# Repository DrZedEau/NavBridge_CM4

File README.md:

# NavBridge CM4

A Raspberry Pi Compute Module 4 carrier board for BMW E-Series vehicles equipped with the OEM navigation system (E46, E39, E85, and similar platforms).

The NavBridge CM4 installs inline between the factory wiring harness and the BMW MK3/MK4 navigation module, allowing a Raspberry Pi Compute Module to integrate with the original infotainment system while preserving the OEM look and functionalities.

Its primary purpose is to provide modern features such as Android Auto and Apple CarPlay through the Raspberry Pi while continuing to use the factory display, controls, and audio system.

This revision is designed for the **Raspberry Pi CM4** and should also work with the **CM5**, which uses the same connectors (see [Using a CM5](#using-a-cm5)).

---

## Overview

The board interfaces directly with the factory navigation module and provides:

- Video output from the Raspberry Pi to the OEM BMW display (analog RGB with sync on green)
- Switching of the display between the factory navigation picture and the Raspberry Pi
- Stereo audio output for integration with the factory AUX input or CDC interface
- Microphone input
- Integration with the BMW I-Bus for power management and button control
- Two M.2 Key E expansion slots
- A CSI camera connector
- An Apple MFi authentication coprocessor

The hardware is designed to run [NavBridge App](https://github.com/DrZedEau/NavBridge_App), a standalone Android Auto head unit for the Raspberry Pi, or the [LIVI](https://github.com/f-io/LIVI) project.

---

## Features

### Hardware

- 100 × 100 mm, 4-layer PCB
- Raspberry Pi CM4 / CM5 connectors (2 × 100-pin Hirose DF40C)
- Automotive-grade 5 V / 3.5 A buck converter (**LMR14030-Q1**), switched on and off by the MCU
- Fused battery input with a **SMCJ24A** TVS diode
- USB-C port for Raspberry Pi flashing (rpiboot) and bench power, with automatic selection between USB-C and the car supply (**TPS2117**)
- 4-port USB 2.0 hub (**USB2514B**) for the MCU, the audio codec and both M.2 slots
- 24-bit video DAC (**ADV7125**) fed by the Raspberry Pi DPI output
- Analog RGB switch (**TMUX1574**) to select the factory navigation picture or the Raspberry Pi picture
- Integrated **PCM2912A** USB audio codec
  - Stereo line output
  - Mono microphone input with bias
- Two M.2 Key E slots, powered by a dedicated 3.3 V / 2 A buck converter (**AP63203**)
  - CN6: PCIe x1 + USB 2.0
  - CN7: USB 2.0 only
- 22-pin CSI camera connector (CAM1, 2 lanes) on the bottom side
- Apple **MFi343S00177** authentication coprocessor on I²C
- Auxiliary 5 V output connector
- SWD connector for the STM32

The board has no SD card slot, so it needs a Compute Module with eMMC (not a Lite module).

### Vehicle Integration

- Two **ATA663231** LIN transceivers: one on the car I-Bus, one on the navigation module's I-Bus, with the MCU in between
- **STM32C071** microcontroller for:
  - Raspberry Pi power management
  - OEM button translation
  - Composite sync (CSYNC) generation for the OEM display
  - Video source selection
- The MCU is powered from the car battery through the car-side LIN transceiver's built-in 3.3 V regulator, so it keeps watching the I-Bus while the Raspberry Pi is off
- No modifications to the factory wiring or infotainment system are required

---

## Board Overview

### Connectors

| Ref | Connector | Use |
|---|---|---|
| CN1, CN2 | Hirose DF40C-100DS | Raspberry Pi CM4 / CM5 |
| CN3 | Molex Micro-Fit 3.0, 12 pins (43045-1200) | To the navigation module |
| CN4 | 2 × 9 pin header, 2.54 mm, right angle | Car harness (X1313 connector) |
| CN5 | 2 × 5 pin header, 1.27 mm | STM32 SWD |
| CN6 | M.2 Key E | PCIe x1 + USB 2.0 module |
| CN7 | M.2 Key E | USB 2.0 module |
| CN8 | JST GH, 2 pins | Auxiliary +5 V output |
| U1 | JST GH, 3 pins | Stereo line output |
| U2 | JST GH, 2 pins | Microphone input |
| U18 | 22-pin FPC, 0.5 mm (bottom side) | CSI camera (CAM1) |
| J1 | USB-C | Raspberry Pi flashing and bench power |

#### CN4 – Car harness

| Pin | Signal | Pin | Signal |
|---|---|---|---|
| 1 | +BATT | 2 | GND |
| 3 | – | 4 | – |
| 5 | I-Bus | 6 | GND |
| 7 | – | 8 | – |
| 9 | Green out | 10 | GND |
| 11 | Blue out | 12 | GND |
| 13 | Red out | 14 | GND |
| 15 | – | 16 | – |
| 17 | Nav audio + | 18 | Nav audio − |

#### CN3 – Navigation module

| Pin | Signal | Pin | Signal |
|---|---|---|---|
| 1 | GND | 7 | +BATT |
| 2 | GND | 8 | I-Bus (navigation side) |
| 3 | GND | 9 | Red in |
| 4 | GND | 10 | Green in |
| 5 | GND | 11 | Blue in |
| 6 | Nav audio − | 12 | Nav audio + |

+BATT and the navigation audio pass straight through between CN3 and CN4. The I-Bus does not: the car I-Bus (CN4 pin 5) and the navigation module's I-Bus (CN3 pin 8) each have their own ATA663231 transceiver, and the STM32 passes messages between them. The red, green and blue signals from the navigation module go through the RGB switch before reaching the display.

#### Audio connectors

| Connector | Pin 1 | Pin 2 | Pin 3 |
|---|---|---|---|
| U2 (microphone) | MIC in | GND | |
| U1 (line out) | Left | GND | Right |
| CN8 (aux power) | +5 V | GND | |

### Buttons and LEDs

| Silkscreen | Part | Function |
|---|---|---|
| nRPIBOOT | SW1 (slide switch) | Pulls the CM `nRPIBOOT` low and routes the CM USB port to the USB-C connector, for flashing with rpiboot |
| RESET | SW2 | STM32 reset |
| BOOT | SW3 | STM32 BOOT0, to start the USB DFU bootloader |
| PWR | D2 (red) | CM power LED |
| ACT | D1 (green) | CM activity LED |
| STAT | D6 (yellow) | STM32 status LED |

### Power

```text
+BATT ─┬─ fuse ─ TVS ─ LMR14030 5 V buck (enabled by MCU) ─┐
       │                                                   ├─ TPS2117 ─ +5 V ─ CM and peripherals
       │                                 USB-C 5 V ────────┘
       │
       └─ diode ─ ATA663231 (car I-Bus) ─ 3.3 V ─┐
                                                 ├─ TPS2117 ─ 3.3 V ─ STM32, RGB switch
                          CM 3.3 V output ───────┘

+5 V ─ TLV75533 LDO ─ 3.3 V ─ USB hub, USB switch, video DAC (through a ferrite bead)
+5 V ─ AP63203 buck ─ 3.3 V ─ M.2 slots, camera
+5 V ─ TPS2051B switch ─ PCM2912A audio codec
```

The battery fuse holder (FH1) takes a Littelfuse 0451003.MRL (3 A) fuse, fitted by hand after assembly.

The TPS2117 selects between the car supply and USB-C automatically, so the board can be powered on the bench from USB-C alone.

### Video

The Raspberry Pi drives the **ADV7125** video DAC through its 24-bit DPI interface. The STM32 combines the DPI `HSYNC` and `VSYNC` into a composite sync (`CSYNC`) with a hardware timer and feeds it to the DAC, which adds it to the green channel (RGsB) as the BMW display expects.

The **TMUX1574** switch, controlled by the STM32, selects which picture reaches the display: the Raspberry Pi or the factory navigation module.

### USB

The CM USB 2.0 port goes through a **TS3USB221** switch controlled by the nRPIBOOT switch:

- **nRPIBOOT off** (normal use): CM → **USB2514B** hub → STM32, PCM2912A codec, M.2 slot CN6, M.2 slot CN7
- **nRPIBOOT on**: CM → USB-C connector, to flash the eMMC with rpiboot

---

## Using a CM5

The CM5 uses the same connectors as the CM4 and keeps the CM4 pinout for the interfaces this board uses (DPI, USB 2.0, PCIe, CSI camera, I²C, `nRPIBOOT`, LEDs), so it should work on this board. It has not been tested yet. A few points to keep in mind:

- The CM5's USB 3.0 ports are not used.
- CSYNC is generated by the STM32, so the board does not rely on the CM5's RP1 PIO as the [CM5 NavBridge](https://github.com/DrZedEau/CM5_NavBridge) did.
- The 5 V rail comes from a 3.5 A buck converter. A CM5 under heavy load, together with power-hungry M.2 or USB devices, can get close to that limit.
- The CM5 runs hotter than the CM4; leave room for a heatsink in the case.

---

## Repository Structure

```text
hardware/      KiCad project (revision 0.2) and the revision 0.1 archive
firmware/      STM32C071 MCU firmware
scripts/       Raspberry Pi setup script
3D/            STL files for printed parts (case and connector)
images/        Pictures and renders
```

The KiCad project in [hardware/](hardware/) was made with KiCad 10 and includes its symbol, footprint and 3D model libraries.

---

## Project Status

Revision 0.2 is the current revision of the CM4 board. Revision 0.1 is kept as an archive in [hardware/](hardware/).

- [x] Schematic and PCB layout
- [ ] Prototype testing
- [ ] STM32 firmware (the CSYNC generator has been validated on a NUCLEO-C071RB)
- [ ] Raspberry Pi setup script
- [ ] 3D printed case and connector

---

## Roadmap

- Test the first prototypes in the car
- Test with a CM5
- Expand compatibility testing across additional BMW platforms

---

## Contributing

Contributions are welcome.

Bug reports, hardware improvements, firmware enhancements, and documentation updates are all appreciated. Please open an issue or submit a pull request if you would like to contribute.

---

## License

Copyright 2026 DrZedEau

The hardware design — the KiCad project in `hardware/`, the 3D printed parts in `3D/` and the images in `images/` — is licensed under the **CERN Open Hardware Licence Version 2 – Strongly Reciprocal** (CERN-OHL-S-2.0), see [LICENSE](LICENSE). You may redistribute and modify it and make products from it under the terms of that licence. It is distributed without any express or implied warranty, including of merchantability, satisfactory quality and fitness for a particular purpose.

Source location: https://github.com/DrZedEau/NavBridge_CM4

As required by section 4 of the CERN-OHL-S, products made from this design must, where practicable, keep this source location visible.

The firmware in `firmware/` and the Raspberry Pi setup script in `scripts/` are licensed under the **GNU General Public License v2.0** (GPL-2.0), see [firmware/LICENSE](firmware/LICENSE) and [scripts/LICENSE](scripts/LICENSE). Third-party files keep their own licences.

---

## References

- CM5 NavBridge (previous board) https://github.com/DrZedEau/CM5_NavBridge
- NavBridge App https://github.com/DrZedEau/NavBridge_App
- LIVI project https://github.com/f-io/LIVI
- Raspberry Pi CM4 datasheet https://datasheets.raspberrypi.com/cm4/cm4-datasheet.pdf
- BMW Wiring Diagram System (WDS) https://bmwteka.com/wds/en/e85/e82460cf
- BMW On-Board Monitor documentation https://bmwteka.com/wds/en/e85/1b7f9876
- Community resources https://www.e46fanatics.com/threads/bmw-on-board-monitor-without-navigation-unit.1303552

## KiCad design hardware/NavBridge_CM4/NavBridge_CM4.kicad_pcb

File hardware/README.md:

# Hardware

KiCad project for the NavBridge CM4 board.

| Path | Content |
|---|---|
| `NavBridge_CM4/` | Revision 0.2 (current): schematics, PCB layout, project-local symbol, footprint and 3D model libraries |
| `NavBridge_CM4/production/` | JLCPCB fabrication files for revision 0.2 (Gerber archive, BOM, pick-and-place), made with the Fabrication Toolkit plugin |
| `NavBridge_CM4_0.1.zip` | Revision 0.1 (archive) |

The project was made with **KiCad 10**. Open `NavBridge_CM4/NavBridge_CM4.kicad_pro`.

The project-local libraries only include the 3D models used on the board. The other models come from the standard KiCad library (`KICAD10_3DMODEL_DIR`, and `KICAD9_3DMODEL_DIR` for a few footprints).

## Board

- 100 × 100 mm, 4 copper layers, 1.6 mm
- 4 × M2.5 mounting holes at the corners (3 mm from each edge)
- 4 × M2.5 mounting holes for the Compute Module
- GND stitching vias around the board edge and across the ground pours
- The battery fuse holder (FH1) takes a Littelfuse 0451003.MRL (3 A) fuse, fitted by hand after assembly

## Schematic sheets

| Sheet | Content |
|---|---|
| NavBridge_CM4 | CM4 / CM5 connectors, car connectors, audio connectors, LEDs, mounting holes |
| Power | Battery input, LMR14030 5 V buck, USB-C connector, TPS2117 power mux, TLV75533 3.3 V LDO |
| MCU_Lin | STM32C071 MCU, two ATA663231 LIN transceivers (car I-Bus and navigation I-Bus), TPS2117 MCU power mux, SWD connector |
| Analog_RGB | ADV7125 video DAC, TMUX1574 RGB switch, 75 Ω termination |
| USB | USB2514B hub, TS3USB221 USB switch |
| Audio | PCM2912A USB audio codec and its power switch |
| M.2 | Two M.2 Key E slots, AP63203 3.3 V buck, auxiliary 5 V connector |
| Misc | Apple MFi authentication coprocessor, CSI camera connector |
| SD_Card | Empty: the SD card slot was removed in revision 0.2 |

## License

CERN-OHL-S-2.0, see [LICENSE](../LICENSE).

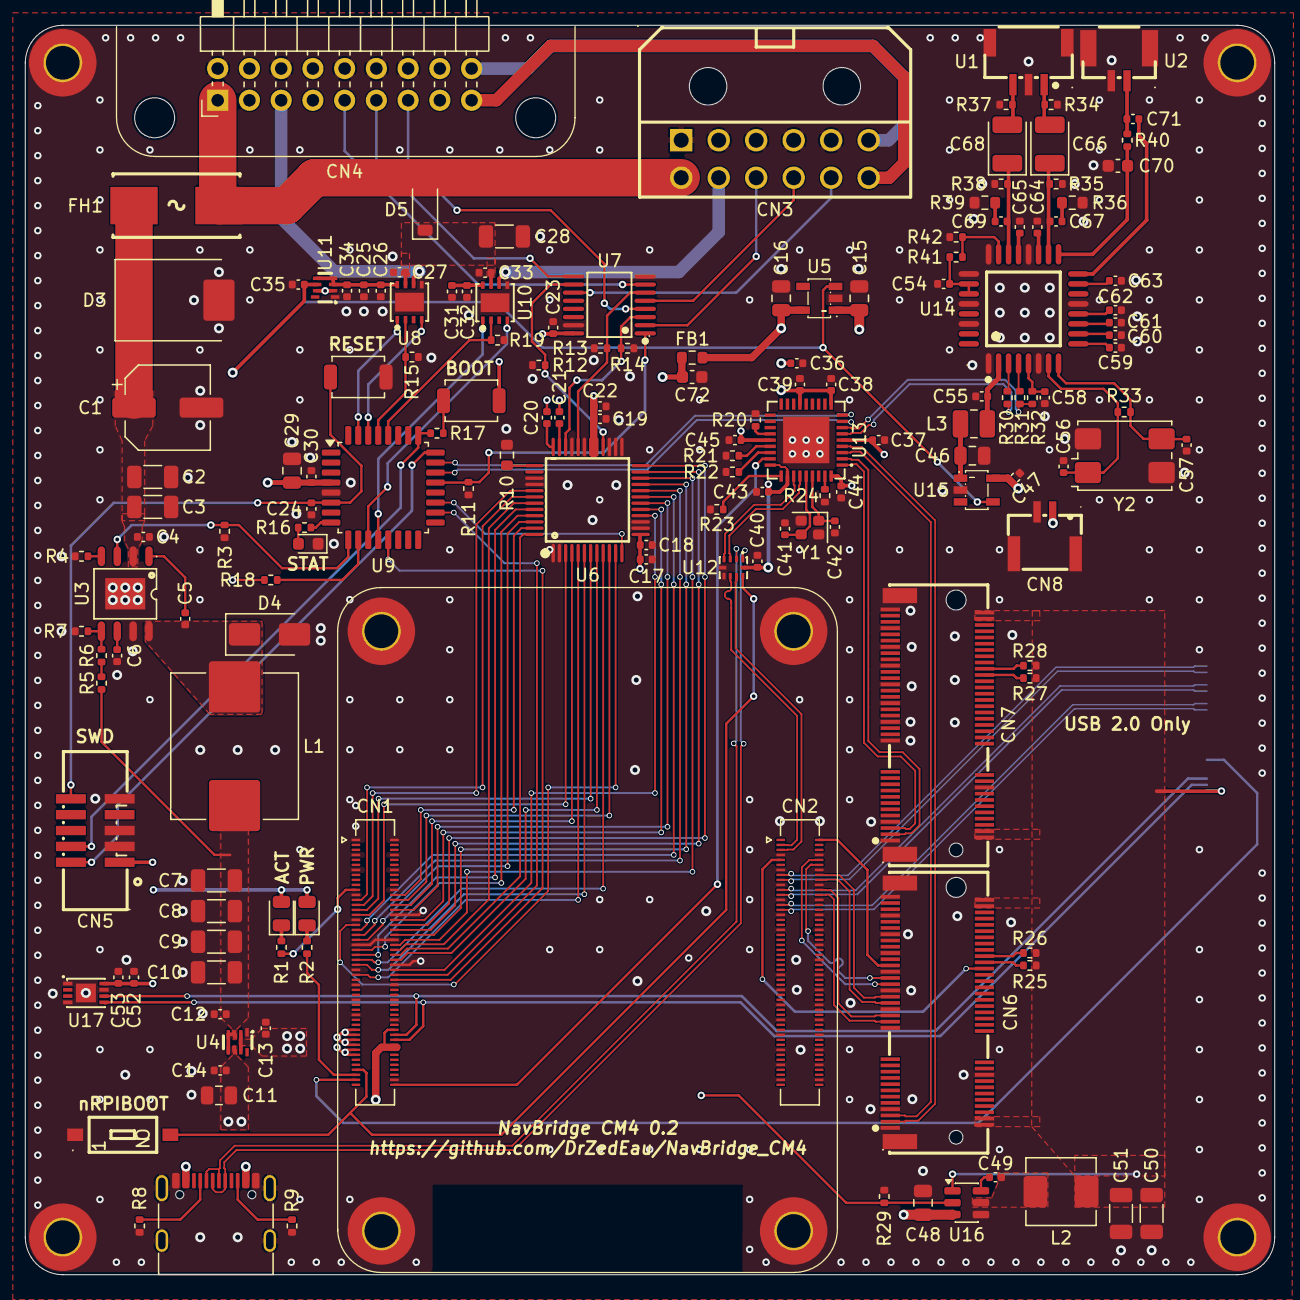
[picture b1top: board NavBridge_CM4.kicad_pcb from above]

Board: 4 copper layers, 100.0 x 100.0 mm, 165 parts (1 on the bottom side), 157 nets.

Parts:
C1: 100µ; CP_Elec_6.3x5.8
C2, C3: 4.7µ; C_1206_3216Metric
C4, C5, C6, C12, C13, C14, C18, C19, C20, C21, C23, C24, C26, C27, C30, C32, C33, C34, C35, C37, C38, C39, C40, C43, C44, C45, C47, C49, C53, C62: 100n; C_0402_1005Metric
C7, C8, C9, C10: 47µ; C_1206_3216Metric
C11, C15, C29: 4.7µ; C_0805_2012Metric
C16, C46, C48: 10µ; C_0805_2012Metric
C17, C22: 10n; C_0402_1005Metric
C25, C31, C61: 4.7µ; C_0402_1005Metric
C28: 10µ; C_1206_3216Metric
C36, C52, C54, C55, C58, C63, C64, C65, C71: 1µ; C_0402_1005Metric
C41, C42: 10p; C_0402_1005Metric
C50, C51: 22µ; C_1206_3216Metric
C56, C57: 22p; C_0402_1005Metric
C59, C60: 100p; C_0402_1005Metric
C66, C68: 100µ; CP_EIA-3528-21_Kemet-B
C67, C69: 22n; C_0402_1005Metric
C70, C72: 10µ; C_0603_1608Metric
CN1, CN2: DF40C-100DS-0.4V; Hirose_DF40C-100DS-0.4V_2x50_P0.4mm
CN3: Molex 430451200; C277636_CONN-TH_12P-P3_00-S3_00_L12_2-W21_7-EH10_7
CN4: X1313 Car connector; PinHeader_2x09_P2.54mm_Horizontal
CN5: 20021521-00010C1LF; C598547_IDC-SMD_10P-P1_27_X1270WVS-2X05B-6TV01
CN6, CN7: 2199230-4_C2977809; C2977809_PCIE-SMD_2199230-4
CN8: BM02B-GHS-TBT (LF)(SN); C161690_CONN-SMD_2P-P1_25_BM02B-GHS-TBT-LF-SN
D1: LED_G; LED_0805_2012Metric
D2: LED_R; LED_0805_2012Metric
D3: SMCJ24A; D_SMC
D4: SS54; D_SMA
D5: 1N4148W; D_SOD-123
D6: LED_Y; LED_0603_1608Metric
FB1: FerriteBead; R_0603_1608Metric
FH1: 01550900M; C108518_FUSE-SMD_L9_8-W5_0_01550900M
H1, H2, H3, H4, H5, H6, H7, H8: MountingHole_Pad; MountingHole_2.7mm_M2.5_Pad_TopBottom
J1: USB_C_Receptacle_USB2.0_16P; USB_C_Receptacle_G-Switch_GT-USB-7010ASV
L1: 6.8uH; L_Sunlord_MWSA1003S
L2: 6.8uH; L_Sunlord_MWSA0518S
L3: 1µH; L_1008_2520Metric
R1, R2, R16, R17, R18, R40: 1k; R_0402_1005Metric
R3, R11, R15, R19, R25, R26, R27, R28, R29: 10k; R_0402_1005Metric
R4: 49.9k; R_0402_1005Metric
R5, R20, R21, R22, R23, R42: 100k; R_0402_1005Metric
R6, R8, R9: 5.1k; R_0402_1005Metric
R7: 18k; R_0402_1005Metric
R10: 560; R_0603_1608Metric
R12, R13, R14: 75; R_0402_1005Metric
R24: 12K; R_0402_1005Metric
R30, R31: 22; R_0402_1005Metric
R32: 1.5k; R_0402_1005Metric
R33: 1M; R_0402_1005Metric
R34, R35, R37, R38: 3.3k; R_0402_1005Metric
R36, R39: 15; R_0603_1608Metric
R41: 0; R_0402_1005Metric
SW1: CHS-01B1; C3312309_SW-SMD_NIDEC_CHS-01B1
SW2, SW3: SW_Push; SW_SPST_TS-1088-xR020
U1: SM03B-GHS; C514175_CONN-TH_SM03B-GHS-TB-LF-SN
U2: SM02B-GHS; C189893_CONN-SMD_SM02B-GHS-TB-LF-SN
U3: LMR14030SQDDARQ1; C485817_SO-8_L4_9-W3_9-P1_27-LS6_0-BL-EP
U4, U11: TPS2117DRLR; C22399676_SOT-583-8_L2_1-W1_2-P0_50-LS1_6-BL
U5: TLV75533PDBVR; C404027_SOT-23-5_L3_0-W1_7-P0_95-LS2_8-BR
U6: ADV7125KSTZ140; LQFP-48_L7.0-W7.0-P0.50-LS9.0-BL
U7: TMUX1574PWR; C2673443_TSSOP-16_L5_0-W4_4-P0_65-LS6_4-BL
U8, U10: ATA663231-GBQW; C5225740_DFN-8_L3_0-W3_0-P0_65-BL-EP-1
U9: STM32C071KBTx; LQFP-32_7x7mm_P0.8mm
U12: TS3USB221ARSER; C128396_UQFN-10_L2_0-W1_5-P0_50-BL
U13: USB2514BI-AEZG-TR; C58940_TQFN-36_L6_0-W6_0-P0_50-BL-EP3_7
U14: PCM2912APJTR; C475497_TQFP-32_L7_0-W7_0-P0_80-LS9_0-TL
U15: TPS2051BDBVR; C24593_SOT-23-5_L3_0-W1_7-P0_95-LS2_8-BR
U16: AP63203WU; TSOT-23-6
U17: MFI343S00177-L; C33770534_DFN-8_L3_0-W2_0-P0_50-BL-EP1_6
U18: 0524352271; C5468341_FPC-SMD_22P-P0_50_0524352271
Y1: Crystal_GND24; Crystal_SMD_2016-4Pin_2.0x1.6mm
Y2: 6MHz; Crystal_SMD_FOX_FQ7050-4Pin_7.0x5.0mm

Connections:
+3V3: C35.1, C52.1, C53.1, CN1.78, CN1.84, CN1.86, CN5.1, D1.2 (A), D2.2 (A), R18.1, R29.1, U5.3 (EN), U11.6 (VIN2), U15.4 (EN), U16.2 (EN), U17.8 (VCC)
+3V3_LDO: C16.1, C36.2, C37.2, C38.2, C39.2, C40.1, C43.1, C44.1, C45.1, FB1.1, U5.5 (OUT), U12.10 (VCC), U13.5 (VDDA33), U13.10 (VDDA33), U13.15 (VDD33), U13.23 (VDD33), U13.27 (VBUS_DET), U13.29 (VDDA33), U13.36 (VDDA33)
+3V3_LIN_REG: C25.1, C26.2, C34.2, U8.8 (VCC), U11.3 (VIN1), U11.4 (PR1), U11.5 (MODE)
+3V3_M2: C50.1, C51.1, CN6.2, CN6.4, CN6.72, CN6.74, CN7.2, CN7.4, CN7.72, CN7.74, L2.2, R25.1, R26.2, R27.1, R28.2, U16.1 (FB), U18.22
+3V3_MUX: C23.2, C29.1, C30.1, SW3.2, U7.16 (VDD), U9.4 (VDD), U11.2 (VOUT), U11.7 (VOUT)
+3V3_SENSE: R18.2, U9.10 (PA3)
+5V: C13.2, C15.2, C47.1, C48.2, CN1.77, CN1.79, CN1.81, CN1.83, CN1.85, CN1.87, CN8.1, U4.2 (VOUT), U4.7 (VOUT), U5.1 (IN), U15.5 (IN), U16.3 (IN)
+5V_BUCK: C7.1, C8.1, C9.1, C10.1, C12.1, L1.2, R5.1, U4.3 (VIN1), U4.4 (PR1), U4.5 (MODE)
+5V_USBC: C11.1, C14.1, J1.A4 (VBUS), J1.A9 (VBUS), J1.B4 (VBUS), J1.B9 (VBUS), U4.6 (VIN2)
+BATT: CN3.7, CN4.1, D5.2 (A), FH1.1
+VBUS_PCM: C46.2, L3.1, U15.1 (OUT)
/Analog_RGB/COMP: C21.2, U6.35 (COMP)
/Analog_RGB/RSET: R10.1, U6.37 (RSET)
/Analog_RGB/VREF: C20.2, U6.36 (VREF)
/Audio/PCM_MBIAS: C70.1, R40.1, U14.17 (MBIAS)
/Audio/PCM_USB_N: R30.2, U14.3 (D-)
/Audio/PCM_USB_P: R31.2, U14.4 (D+)
/Audio/PCM_VBUS: C55.1, L3.2, U14.2 (VBUS)
/Audio/PCM_VCCL: C64.1, U14.19 (VCCL)
/Audio/PCM_VCCR: C65.1, U14.21 (VCCR)
/Audio/PCM_VDD: C58.1, R32.2, U14.5 (VDD)
/Audio/PCM_VIN: C71.2, U14.16 (VIN)
/Audio/PCM_VOUTL: C66.1, C67.1, R35.2, U14.18 (VOUTL)
/Audio/PCM_VOUTR: C68.1, C69.1, R38.2, U14.22 (VOUTR)
/Audio/PCM_XTI: C57.1, R33.2, U14.8 (XTI), Y2.3
/Audio/PCM_XTO: C56.1, R33.1, U14.7 (XTO), Y2.1
/LED1: D1.1 (K), R1.1
/LED2: D2.1 (K), R2.1
/LED_nACT: CN1.21, R1.2
/LED_nPWR: CN1.95, R2.2
/M.2/BST_3V3: C49.1, U16.6 (BST)
/M.2/SW_3V3: C49.2, L2.1, U16.5 (SW)
/Power/+BATT_FUSED: C1.1, C2.1, C3.1, C4.1, D3.1 (K), FH1.2, U3.2 (VIN)
/Power/BOOT: C5.1, U3.1 (BOOT)
/Power/FB: R6.2, R7.1, U3.5 (FB)
/Power/FREQ: R4.1, U3.4 (RT/SYNC)
/Power/SS: C6.1, U3.6 (SS)
/Power/SW: C5.2, D4.1 (K), L1.1, U3.8 (SW)
AUDIO_L: C66.2, R34.2, U1.1
AUDIO_R: C68.2, R37.1, U1.3
B0: CN1.54, U6.16 (B0)
B1: CN1.34, U6.17 (B1)
B2: CN1.30, U6.18 (B2)
B3: CN1.37, U6.19 (B3)
B4: CN1.39, U6.20 (B4)
B5: CN1.40, U6.21 (B5)
B6: CN1.44, U6.22 (B6)
B7: CN1.38, U6.23 (B7)
B_NAV: CN3.11, U7.11 (S3A)
B_OUT: CN4.11, U7.9 (D3)
B_RPI: R12.2, U6.28 (IOB), U7.10 (S3B)
CAM1_C_N: CN2.27, U18.8
CAM1_C_P: CN2.29, U18.9
CAM1_D0_N: CN2.15, U18.2
CAM1_D0_P: CN2.17, U18.3
CAM1_D1_N: CN2.21, U18.5
CAM1_D1_P: CN2.23, U18.6
CSYNC: U6.12 (~SYNC), U9.19 (PA9)
Camera_GPIO: CN1.97, U18.17
DEN: CN1.35, U6.11 (~BLANK)
G0: CN1.31, U6.3 (G0)
G1: CN1.28, U6.4 (G1)
G2: CN1.55, U6.5 (G2)
G3: CN1.51, U6.6 (G3)
G4: CN1.29, U6.7 (G4)
G5: CN1.50, U6.8 (G5)
G6: CN1.49, U6.9 (G6)
G7: CN1.26, U6.10 (G7)
GND: C1.2, C2.2, C3.2, C4.2, C6.2, C7.2, C8.2, C9.2, C10.2, C11.2, C12.2, C13.1, C14.2, C15.1, C16.2, C17.1, C18.1, C19.1, C22.1, C23.1, C24.1, C25.2, C26.1, C27.1, C28.2, C29.2, C30.2, C31.2, C32.2, C33.1, C34.1, C35.2, C36.1, C37.1, C38.1, C39.1, C40.2, C41.2, C42.2, C43.2, C44.2, C45.2, C46.1, C47.2, C48.1, C50.2, C51.2, C52.2, C53.2, C54.2, C55.2, C56.2, C57.2, C58.2, C59.2, C60.2, C61.2, C62.2, C63.2, C64.2, C65.2, C70.2, C72.1, CN1.1, CN1.2, CN1.7, CN1.8, CN1.13, CN1.14, CN1.22, CN1.23, CN1.32, CN1.33, CN1.42, CN1.43, CN1.52, CN1.53, CN1.59, CN1.60, CN1.65, CN1.66, CN1.71, CN1.74, CN1.98, CN2.7, CN2.8, CN2.13, CN2.14, CN2.19, CN2.20, CN2.25, CN2.26, CN2.31, CN2.32, CN2.37, CN2.38, CN2.44, CN2.50, CN2.55, CN2.56, CN2.61, CN2.62, CN2.67, CN2.68, CN2.73, CN2.74, CN2.79, CN2.80, CN2.85, CN2.86, CN2.91, CN2.92, CN2.97, CN2.98, CN3.1, CN3.2, CN3.3, CN3.4, CN3.5, CN4.2, CN4.6, CN4.10, CN4.12, CN4.14, CN5.3, CN5.5, CN5.9, CN6.1, CN6.7, CN6.18, CN6.33, CN6.39, CN6.45, CN6.51, CN6.57, CN6.63, CN6.69, CN6.75, CN6.76, CN6.77, CN7.1, CN7.7, CN7.18, CN7.33, CN7.39, CN7.45, CN7.51, CN7.57, CN7.63, CN7.69, CN7.75, CN7.76, CN7.77, CN8.2, CN8.3, CN8.4, D3.2 (A), D4.2 (A), D6.1 (K), H1.1 (1_1), H2.1 (1_1), H3.1 (1_1), H4.1 (1_1), H5.1 (1_1), H6.1 (1_1), H7.1 (1_1), H8.1 (1_1), J1.A1 (GND), J1.A12 (GND), J1.B1 (GND), J1.B12 (GND), J1.SH (SHIELD), R3.2, R4.2, R7.2, R8.2, R9.2, R10.2, R11.2, R12.1, R13.1, R14.1, R15.2, R19.2, R20.1, R21.2, R22.1, R23.2, R24.2, R29.2, R34.1, R35.1, R36.2, R37.2, R38.1, R39.2, R42.2, SW1.1 (PIN1), SW2.1, U1.2, U1.4, U1.5, U2.2, U2.3, U2.4, U3.7 (GND), U3.9 (EP), U4.1 (GND), U5.2 (GND), U6.1 (GND), U6.2 (GND), U6.14 (GND), U6.15 (GND), U6.25 (GND), U6.26 (GND), U6.27 (~IOB), U6.31 (~IOG), U6.33 (~IOR), U6.39 (GND), U6.40 (GND), U7.8 (GND), U7.15 (EN#), U8.5 (GND), U8.9 (EP), U9.5 (VSS), U10.5 (GND), U10.9 (EP), U11.1 (GND), U12.5 (GND), U12.6 (OE#), U13.37 (EP), U14.1 (BGND), U14.6 (DGND), U14.13 (AGND), U14.20 (HGND), U14.24 (POWER), U14.25 (PGND), U14.28 (TEST0), U14.30 (MMUTE), U15.2 (GND), U16.4 (GND), U17.1 (GND), U17.4 (GND), U17.7 (GND), U17.9 (EP), U18.1, U18.4, U18.7, U18.10, U18.13, U18.16, U18.19, U18.23, U18.24, Y1.2 (G), Y1.4 (G), Y2.2 (G), Y2.4 (G)
G_NAV: CN3.10, U7.5 (S2A)
G_OUT: CN4.9, U7.7 (D2)
G_RPI: R13.2, U6.32 (IOG), U7.6 (S2B)
HSYNC: CN1.56, U9.18 (PA8)
IBUS_CAR: CN4.5, U8.6 (LIN)
IBUS_NAV: CN3.8, U10.6 (LIN)
MCU_BUCK_EN: R3.1, U3.3 (EN), U9.9 (PA2)
MCU_LIN1_EN: R15.1, U8.2 (EN), U9.29 (PB5)
MCU_LIN1_RX: U8.1 (RXD), U9.31 (PB7)
MCU_LIN1_TX: U8.4 (TXD), U9.30 (PB6)
MCU_LIN2_EN: R19.1, U9.28 (PB4), U10.2 (EN)
MCU_LIN2_RX: U9.12 (PA5), U10.1 (RXD)
MCU_LIN2_TX: U9.11 (PA4), U10.4 (TXD)
MCU_SWITCHER_IN: R11.1, U7.1 (SEL), U9.21 (PA10)
MIC_IN: C71.1, R40.2, U2.1
NAV_AUDIO_NEG: CN3.6, CN4.18
NAV_AUDIO_POS: CN3.12, CN4.17
NRST: C24.2, CN5.10, SW2.2, U9.6 (PF2)
unnamed: C17.2, C18.2, C19.2, C20.1, C21.1, C22.2, C72.2, FB1.2, U6.13 (VAA), U6.29 (VAA), U6.30 (VAA)
unnamed: C67.2, R36.1
unnamed: C69.2, R39.1
unnamed: CN6.54, R25.2
unnamed: CN6.56, R26.1
unnamed: CN7.54, R27.2
unnamed: CN7.56, R28.1
unnamed: D6.2 (A), R16.2
unnamed: J1.A5 (CC1), R8.1
unnamed: J1.B5 (CC2), R9.1
unnamed: R5.2, R6.1
unnamed: R17.1, SW3.1
unnamed: R16.1, U9.8 (PA1)
unnamed: C31.1, C32.1, U10.8 (VCC)
unnamed: R22.2, U13.25 (HS_IND/CFG_SEL1)
unnamed: R24.1, U13.35 (RBIAS)
unnamed: R21.1, U13.24 (SCL/SMBCLK/CFG_SEL0)
unnamed: R20.2, U13.22 (SDA/SMBBATA/NON_REM1)
unnamed: R23.1, U13.28 (SUSP_IND/LOCAL_PWR/NON_REM0)
unnamed: C59.1, U14.9 (FL)
unnamed: C60.1, U14.10 (FR)
unnamed: R41.2, R42.1, U14.23 (MAMP)
unnamed: C54.1, R41.1, U14.26 (VCCP), U14.27 (TEST1)
unnamed: C63.1, U14.15 (VCCA)
unnamed: C61.1, U14.11 (VCOM1)
unnamed: C62.1, U14.12 (VCOM2)
PCIe_CLK_N: CN2.12, CN6.49
PCIe_CLK_P: CN2.10, CN6.47
PCIe_CLK_nREQ: CN2.2, CN6.53
PCIe_RX_N: CN2.18, CN6.41
PCIe_RX_P: CN2.16, CN6.43
PCIe_TX_N: CN2.24, CN6.35
PCIe_TX_P: CN2.22, CN6.37
PCIe_nRST: CN2.9, CN6.52
PCLK: CN1.36, U6.24 (CLOCK)
R0: CN1.27, U6.41 (R0)
R1: CN1.25, U6.42 (R1)
R2: CN1.46, U6.43 (R2)
R3: CN1.47, U6.44 (R3)
R4: CN1.45, U6.45 (R4)
R5: CN1.41, U6.46 (R5)
R6: CN1.24, U6.47 (R6)
R7: CN1.48, U6.48 (R7)
RPI_SCL: CN1.80, U17.6 (SCL), U18.20
RPI_SDA: CN1.82, U17.5 (SDA), U18.21
R_NAV: CN3.9, U7.2 (S1A)
R_OUT: CN4.13, U7.4 (D1)
R_RPI: R14.2, U6.34 (IOR), U7.3 (S1B)
SWCLK: CN5.4, R17.2, U9.25 (PA14)
SWDIO: CN5.2, U9.24 (PA13)
USB_C_N: J1.A7 (D-), J1.B7 (D-), U12.2 (1D-)
USB_C_P: J1.A6 (D+), J1.B6 (D+), U12.1 (1D+)
USB_HUB_N: U12.4 (2D-), U13.30 (USBDM_UP)
USB_HUB_P: U12.3 (2D+), U13.31 (USBDP_UP)
USB_HUB_XTALIN: C42.1, U13.33 (XTALIN/CLKIN), Y1.1
USB_HUB_XTALOUT: C41.1, U13.32 (XTALOUT), Y1.3
USB_MCU_N: U9.22 (PA11), U13.8 (USBDM_DN4/PRT_DIS_M4)
USB_MCU_P: U9.23 (PA12), U13.9 (USBDP_DN4/PRT_DIS_P4)
USB_N: CN2.3, U12.7 (D-)
USB_P: CN2.5, U12.8 (D+)
USB_PCM_N: R30.1, U13.6 (USBDM_DN3/PRT_DIS_M3)
USB_PCM_P: R31.1, R32.1, U13.7 (USBDP_DN3/PRT_DIS_P3)
USB_SLOT1_N: CN7.5, U13.1 (USBDM_DN1/PRT_DIS_M1)
USB_SLOT1_P: CN7.3, U13.2 (USBDP_DN1/PRT_DIS_P1)
USB_SLOT2_N: CN6.5, U13.3 (USBDM_DN2/PRT_DIS_M2)
USB_SLOT2_P: CN6.3, U13.4 (USBDP_DN2/PRT_DIS_P2)
VS: C27.2, C28.1, C33.2, D5.1 (K), U8.7 (VS), U10.7 (VS)
VSYNC: CN1.58, U9.13 (PA6)
nEXTRST: CN1.100, U13.26 (RESET_N)
nRPIBOOT: CN1.93, SW1.2 (PIN2), U12.9 (S)

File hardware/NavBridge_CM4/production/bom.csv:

Designator,Footprint,Quantity,Value,LCSC Part #
C1,CP_Elec_6.3x5.8,1,100µ,C128464
"C10, C7, C8, C9",1206,4,47µ,C96123
"C11, C15, C29",0805,3,4.7µ,C1779
"C12, C13, C14, C18, C19, C20, C21, C23, C24, C26, C27, C30, C32, C33, C34, C35, C37, C38, C39, C4, C40, C43, C44, C45, C47, C49, C5, C53, C6, C62",0402,30,100n,C307331
"C16, C46, C48",0805,3,10µ,C15850
"C17, C22",0402,2,10n,C15195
"C2, C3",1206,2,4.7µ,C29823
"C25, C31, C61",0402,3,4.7µ,C23733
C28,1206,1,10µ,C13585
"C36, C52, C54, C55, C58, C63, C64, C65, C71",0402,9,1µ,C52923
"C41, C42",0402,2,10p,C32949
"C50, C51",1206,2,22µ,C12891
"C56, C57",0402,2,22p,C1555
"C59, C60",0402,2,100p,C1546
"C66, C68",CP_EIA-3528-21_Kemet-B,2,100µ,C16133
"C67, C69",0402,2,22n,C1532
C70,0603,1,10µ,C96446
C72,0603,1,10µ,C19702
"CN1, CN2",Hirose_DF40C-100DS-0.4V_2x50_P0.4mm,2,DF40C-100DS-0.4V,C597931
CN3,C277636_CONN-TH_12P-P3_00-S3_00_L12_2-W21_7-EH10_7,1,Molex 430451200,C277636
CN4,PinHeader_2x09_P2.54mm_Horizontal,1,X1313 Car connector,C492437
CN5,C598547_IDC-SMD_10P-P1_27_X1270WVS-2X05B-6TV01,1,20021521-00010C1LF,C598547
"CN6, CN7",C2977809_PCIE-SMD_2199230-4,2,2199230-4_C2977809,C2977809
CN8,C161690_CONN-SMD_2P-P1_25_BM02B-GHS-TBT-LF-SN,1,BM02B-GHS-TBT (LF)(SN),C161690
D1,0805,1,LED_G,C2297
D2,0805,1,LED_R,C84256
D3,D_SMC,1,SMCJ24A,C19077604
D4,D_SMA,1,SS54,C22452
D5,D_SOD-123,1,1N4148W,C81598
D6,0603,1,LED_Y,C89811
FB1,0603,1,FerriteBead,C14709
FH1,C108518_FUSE-SMD_L9_8-W5_0_01550900M,1,01550900M,C108518
J1,USB_C_Receptacle_G-Switch_GT-USB-7010ASV,1,USB_C_Receptacle_USB2.0_16P,C2988369
L1,L_Sunlord_MWSA1003S,1,6.8uH,C2453947
L2,L_Sunlord_MWSA0518S,1,6.8uH,C2928918
L3,1008,1,1µH,C435392
"R1, R16, R17, R18, R2, R40",0402,6,1k,C11702
R10,0603,1,560,C23204
"R11, R15, R19, R25, R26, R27, R28, R29, R3",0402,9,10k,C25744
"R12, R13, R14",0402,3,75,C25133
"R20, R21, R22, R23, R42, R5",0402,6,100k,C25741
R24,0402,1,12K,C25752
"R30, R31",0402,2,22,C25092
R32,0402,1,1.5k,C25867
R33,0402,1,1M,C26083
"R34, R35, R37, R38",0402,4,3.3k,C25890
"R36, R39",0603,2,15,C22810
R4,0402,1,49.9k,C25897
"R6, R8, R9",0402,3,5.1k,C25905
R7,0402,1,18k,C25762
SW1,C3312309_SW-SMD_NIDEC_CHS-01B1,1,CHS-01B1,C3312309
SW2,SW_SPST_TS-1088-xR020,1,SW_Push,C318884
SW3,SW_SPST_TS-1088-xR020,1,SW_Push,C720477
U1,C514175_CONN-TH_SM03B-GHS-TB-LF-SN,1,SM03B-GHS,C514175
"U10, U8",C5225740_DFN-8_L3_0-W3_0-P0_65-BL-EP-1,2,ATA663231-GBQW,C5225740
"U11, U4",C22399676_SOT-583-8_L2_1-W1_2-P0_50-LS1_6-BL,2,TPS2117DRLR,C22399676
U12,C128396_UQFN-10_L2_0-W1_5-P0_50-BL,1,TS3USB221ARSER,C128396
U13,C58940_TQFN-36_L6_0-W6_0-P0_50-BL-EP3_7,1,USB2514BI-AEZG-TR,C58940
U14,C475497_TQFP-32_L7_0-W7_0-P0_80-LS9_0-TL,1,PCM2912APJTR,C475497
U15,C24593_SOT-23-5_L3_0-W1_7-P0_95-LS2_8-BR,1,TPS2051BDBVR,C24593
U16,TSOT-23-6,1,AP63203WU,C780769
U17,C33770534_DFN-8_L3_0-W2_0-P0_50-BL-EP1_6,1,MFI343S00177-L,C33770534
U18,C5468341_FPC-SMD_22P-P0_50_0524352271,1,0524352271,C5468341
U2,C189893_CONN-SMD_SM02B-GHS-TB-LF-SN,1,SM02B-GHS,C189893
U3,C485817_SO-8_L4_9-W3_9-P1_27-LS6_0-BL-EP,1,LMR14030SQDDARQ1,C485817
U5,C404027_SOT-23-5_L3_0-W1_7-P0_95-LS2_8-BR,1,TLV75533PDBVR,C404027
U6,LQFP-48_L7.0-W7.0-P0.50-LS9.0-BL,1,ADV7125KSTZ140,C9668
U7,C2673443_TSSOP-16_L5_0-W4_4-P0_65-LS6_4-BL,1,TMUX1574PWR,C2673443
U9,LQFP-32_7x7mm_P0.8mm,1,STM32C071KBTx,C42116633
Y1,Crystal_SMD_2016-4Pin_2.0x1.6mm,1,Crystal_GND24,C6616880
Y2,Crystal_SMD_FOX_FQ7050-4Pin_7.0x5.0mm,1,6MHz,C179631
